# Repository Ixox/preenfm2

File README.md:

# preenfm2 firmware

Ixox/preenfm2 is the official repository of the preenfm2 firmware.

You can find here the compiled firmware, its code source and some hardware files for the PCB, MCU board and cases.

To flash the preenfm2 for the first time, [follow these instructions](https://github.com/Ixox/preenfm2/tree/master/flash)

## Compiling the firmware

To compile the firmware, you'll need [arm-gcc version 4.7](https://launchpad.net/gcc-arm-embedded/+milestone/4.7-2014-q2-update)

Add the bin directory to your PATH, and run **'make'**, you'll get the list of the available targets.

```bash
$ make
You must chose a target 
Don't forget to clean between different build targets
   clean : clean build directory
   pfm : build pfm2 firmware
   pfmcv : build pfm2 firmware for Eurorack 
   installdfu : flash last compiled firmware through DFU
   zip : create zip with all inside
```
Since some refactoring, the bootloader does not compile anymore. But it's available in its binary format.

Then put your preenfm2 in [bootloader mode](http://ixox.fr/preenfm2/manual/upgrade-firmware/). Look at DFU part 4.

To flash the firmware on the preenfm2 using the DFU protocol :

```bash
make installdfu
```

Once it's done, unplug the power cable and plug it back.

## New Filters in 2.11

Many effects have been added in the firmware 2.11. They were coded by [Toltekradiation](http://ixox.fr/forum/index.php?topic=69544.0).

His github repo is [here](https://github.com/pvig/preenfm2). You'll find there some description of the different effects.

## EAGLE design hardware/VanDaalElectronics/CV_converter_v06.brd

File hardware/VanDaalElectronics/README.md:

# Eurorack PCB eagle files for the preenfm2

Here is the first revision Eagle files for the Eurorack daughter board.
This board converts Modulation inputs (cv3 and CV4) -5V to +5V for Preen AIN
It handles V/Oct 0-8V from CV2 to AIN and Gate from CV1 to AIN.

All the unnamed diodes are general purpose diodes.
Shotky diodes are also what ever fits. As long it has very low forward voltage.

CV inputs can be wired straight to 3.5mm jacks.
Same with MIDI and USB.

+5V needs to be routed to the mainboard.

[Van Daal Electronics DIY Kit](https://vandaal-electronics.com/product/preenfm-eurorack-retrofit-diy-kit/)

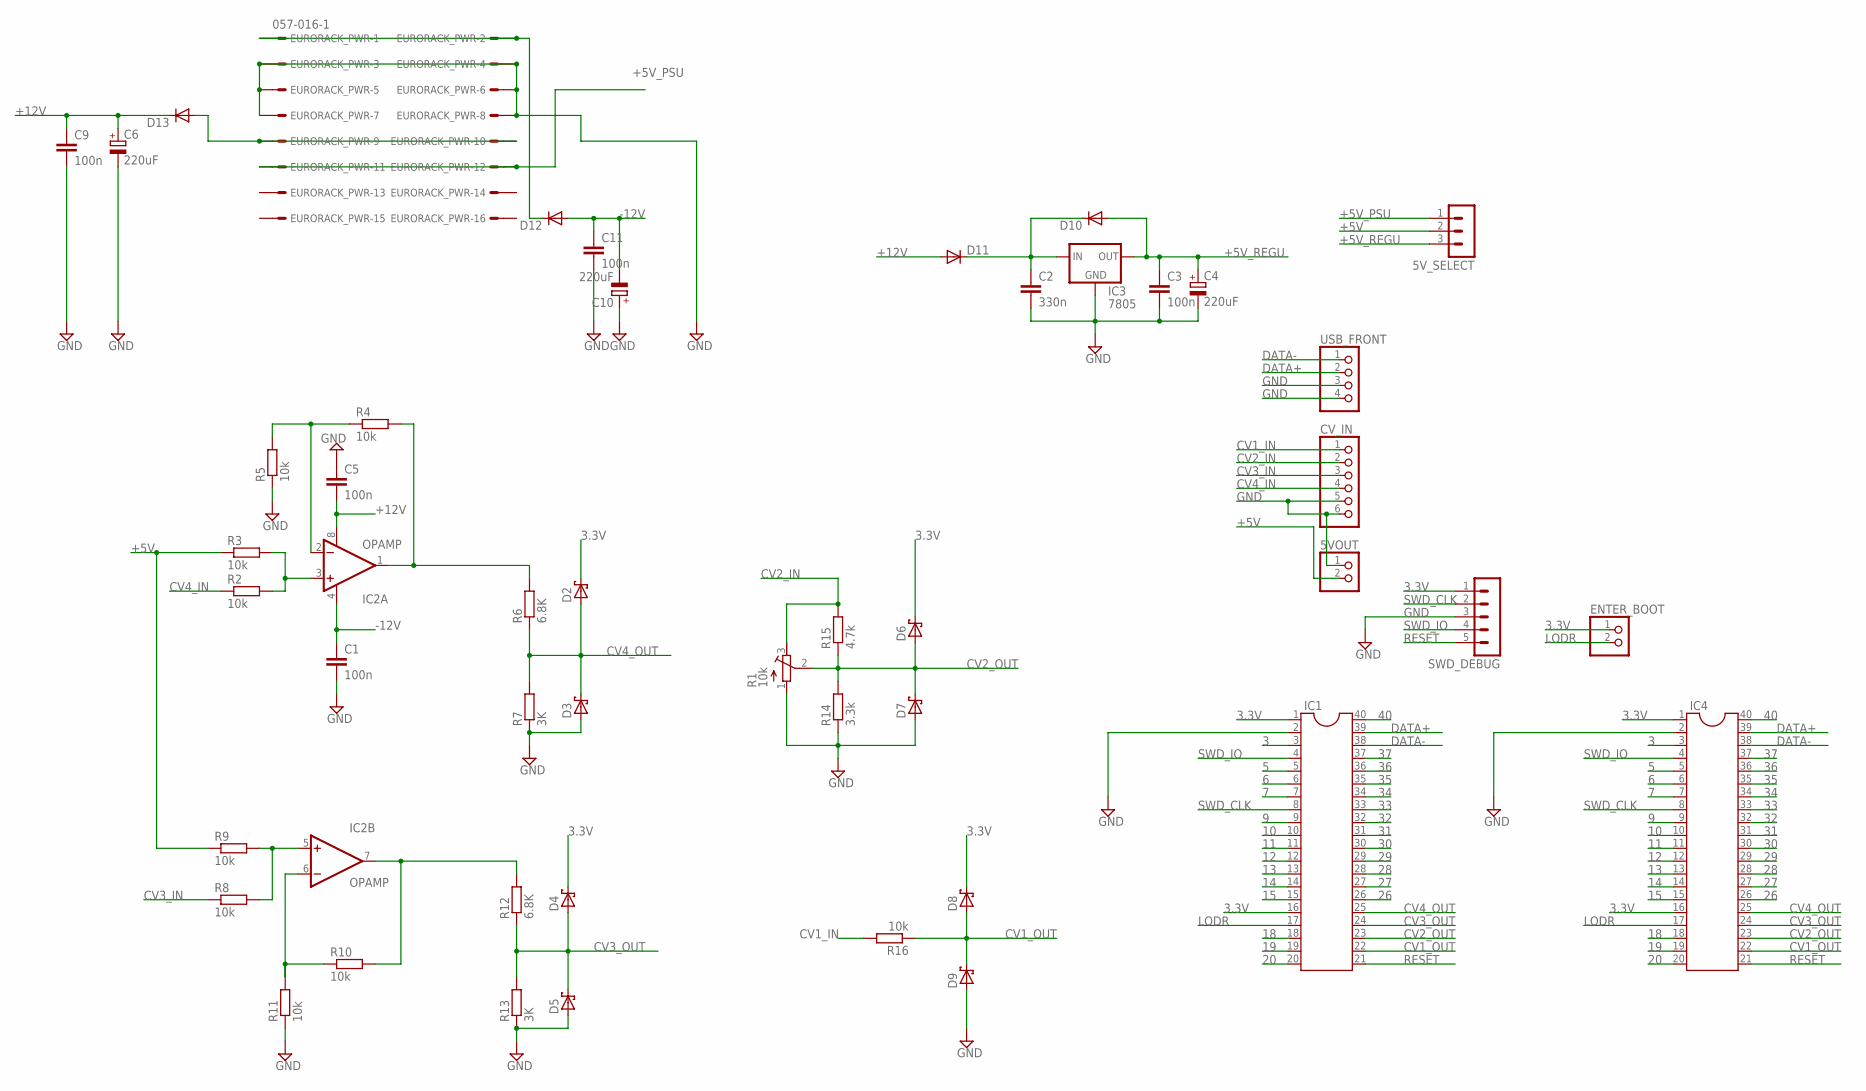
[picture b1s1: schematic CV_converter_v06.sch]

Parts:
5VOUT: PINHD-1X2; 1X02
5V_SELECT: MA03-1
C1, C3, C5, C9, C11: 100n; C025-025X050
C2: 330n; C025-025X050
C4, C6, C10: 220uF; E2,5-7
CV_IN: PINHD-1X6; 1X06
D2, D3, D4, D5, D6, D7, D8, D9: SCHOTTKY-DIODEDO35-7; DO35-7
D10, D11, D12, D13: DIODE-D-7.5; D-7.5
ENTER_BOOT: PINHD-1X2; 1X02
EURORACK_PWR: 057-016-1
IC1, IC4: DIL40
IC2: OPAMP; DIP08
IC3: 7805; TO-220-ALT
R1: 10k; RTRIM64W
R2, R3, R4, R5, R8, R9, R10, R11, R16: 10k; 0207/7
R6, R12: 6.8K; 0207/7
R7, R13: 3K; 0207/7
R14: 3.3k; 0207/7
R15: 4.7k; 0207/7
SWD_DEBUG: MA05-1
USB_FRONT: PINHD-1X4; 1X04

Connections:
3: IC1.3, IC4.3
3.3V: D2.C, D4.C, D6.C, D8.C, ENTER_BOOT.1, IC1.1, IC1.16, IC4.1, IC4.16, SWD_DEBUG.1
5: IC1.5, IC4.5
6: IC1.6, IC4.6
7: IC1.7, IC4.7
9: IC1.9, IC4.9
10: IC1.10, IC4.10
11: IC1.11, IC4.11
12: IC1.12, IC4.12
13: IC1.13, IC4.13
14: IC1.14, IC4.14
15: IC1.15, IC4.15
18: IC1.18, IC4.18
19: IC1.19, IC4.19
20: IC1.20, IC4.20
26: IC1.26, IC4.26
27: IC1.27, IC4.27
28: IC1.28, IC4.28
29: IC1.29, IC4.29
30: IC1.30, IC4.30
31: IC1.31, IC4.31
32: IC1.32, IC4.32
33: IC1.33, IC4.33
34: IC1.34, IC4.34
35: IC1.35, IC4.35
36: IC1.36, IC4.36
37: IC1.37, IC4.37
40: IC1.40, IC4.40
+5V: 5VOUT.2, 5V_SELECT.2, R3.1, R9.1
+5V_PSU: 5V_SELECT.1, EURORACK_PWR.11, EURORACK_PWR.12
+5V_REGU: 5V_SELECT.3, C3.1, C4.+, D10.A, IC3.OUT
+12V: C5.2, C6.+, C9.1, D11.A, D13.C, IC2.8 (V+)
-12V: C1.1, C10.-, C11.1, D12.A, IC2.4 (V-)
CV1_IN: CV_IN.1, R16.2
CV1_OUT: D8.A, D9.C, IC1.22, IC4.22, R16.1
CV2_IN: CV_IN.2, R1.3 (E), R15.2
CV2_OUT: D6.A, D7.C, IC1.23, IC4.23, R1.2 (S), R14.2, R15.1
CV3_IN: CV_IN.3, R8.1
CV3_OUT: D4.A, D5.C, IC1.24, IC4.24, R12.1, R13.2
CV4_IN: CV_IN.4, R2.1
CV4_OUT: D2.A, D3.C, IC1.25, IC4.25, R6.1, R7.2
DATA+: IC1.39, IC4.39, USB_FRONT.2
DATA-: IC1.38, IC4.38, USB_FRONT.1
GND: 5VOUT.1, C1.2, C2.2, C3.2, C4.-, C5.1, C6.-, C9.2, C10.+, C11.2, CV_IN.5, CV_IN.6, D3.A, D5.A, D7.A, D9.A, EURORACK_PWR.3, EURORACK_PWR.4, EURORACK_PWR.5, EURORACK_PWR.6, EURORACK_PWR.7, EURORACK_PWR.8, IC1.2, IC3.GND, IC4.2, R1.1 (A), R5.1, R7.1, R11.1, R13.1, R14.1, SWD_DEBUG.3, USB_FRONT.3, USB_FRONT.4
LODR: ENTER_BOOT.2, IC1.17, IC4.17
unnamed: IC2.1 (OUT), R4.2, R6.2
unnamed: IC2.3 (+IN), R2.2, R3.2
unnamed: C2.1, D10.C, D11.C, IC3.IN
unnamed: IC2.2 (-IN), R4.1, R5.2
unnamed: IC2.6 (-IN), R10.1, R11.2
unnamed: IC2.7 (OUT), R10.2, R12.2
unnamed: IC2.5 (+IN), R8.2, R9.2
unnamed: D12.C, EURORACK_PWR.1, EURORACK_PWR.2
unnamed: D13.A, EURORACK_PWR.9, EURORACK_PWR.10
RESET: IC1.21, IC4.21, SWD_DEBUG.5
SWD_CLK: IC1.8, IC4.8, SWD_DEBUG.2
SWD_IO: IC1.4, IC4.4, SWD_DEBUG.4

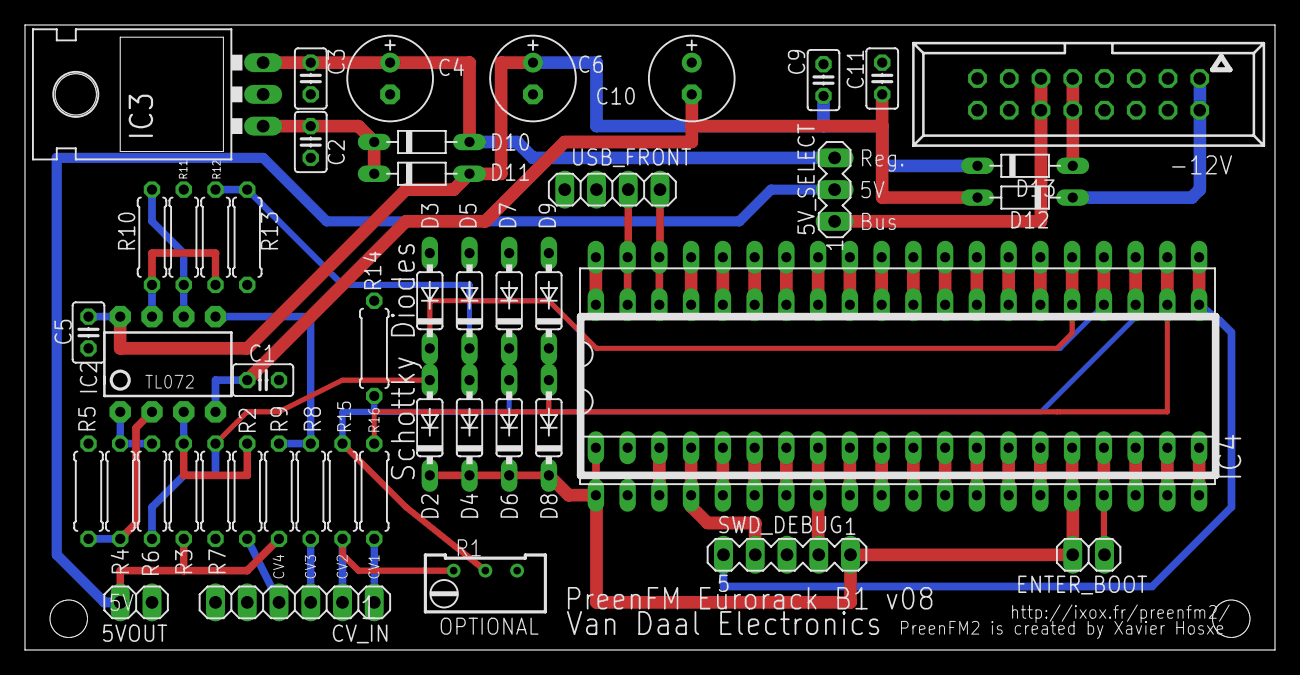
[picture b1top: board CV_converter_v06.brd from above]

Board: 2 copper layers, 100.0 x 50.0 mm, 48 parts (0 on the bottom side), 57 nets.

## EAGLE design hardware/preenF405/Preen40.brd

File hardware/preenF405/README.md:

'''html
### PreenF405

Here is the schematic and board of the preenFM microcontroller board.
Files have been created with eagle 6.5.

The BOM used for the official preenF405 is :
<pre>
Manufacturer       Part Number         Designator        Qty  Desciption                       Case            Top/bot Points
Yageo              CC0603KRX7R9BB104   C1, C2, C3, C4    4    100nF,50V,10%,X7R,0603           0603     SMD    Top     2    
Murata             GRM1885C1H200FA01D  C6, C7            2    20pF,50V,1%,C0G,0603             0603     SMD    Top     2    
TDK Corporation    C2012X7R1H225K125AC C8, C9            2    2.2uF,50V,10%,X7R,0805           0805     SMD    Top     2    
Kemet              T491B106K016AT      C10               1    10uF,16V,10%,1411(B)             1411(B)  SMD    Top     2    
Yageo              RC0603FR-0710KL     R1, R2, R3, R6    4    10K,1%,1/10W,0603                0603     SMD    Top     2    
Yageo              RC0603FR-0722RL     R4, R5            2    22R,1%,1/10W,0603                0603     SMD    Top     2    
TXC Corporation    AT-12.000MAGK-T     QA                1    12MHz,20pF,HC49/US               HC49/US  SMD    Top     2    
STMicroelectronics STM32F405RGT6       IC1               1    STM32F405RGT6,64-LQFP            64-LQFP  SMD    Top     64   
TAD                1-2001FBV0T                           2    1*20 Pins,Pitches 2.54mm,180°                    Bot     20   
</pre>

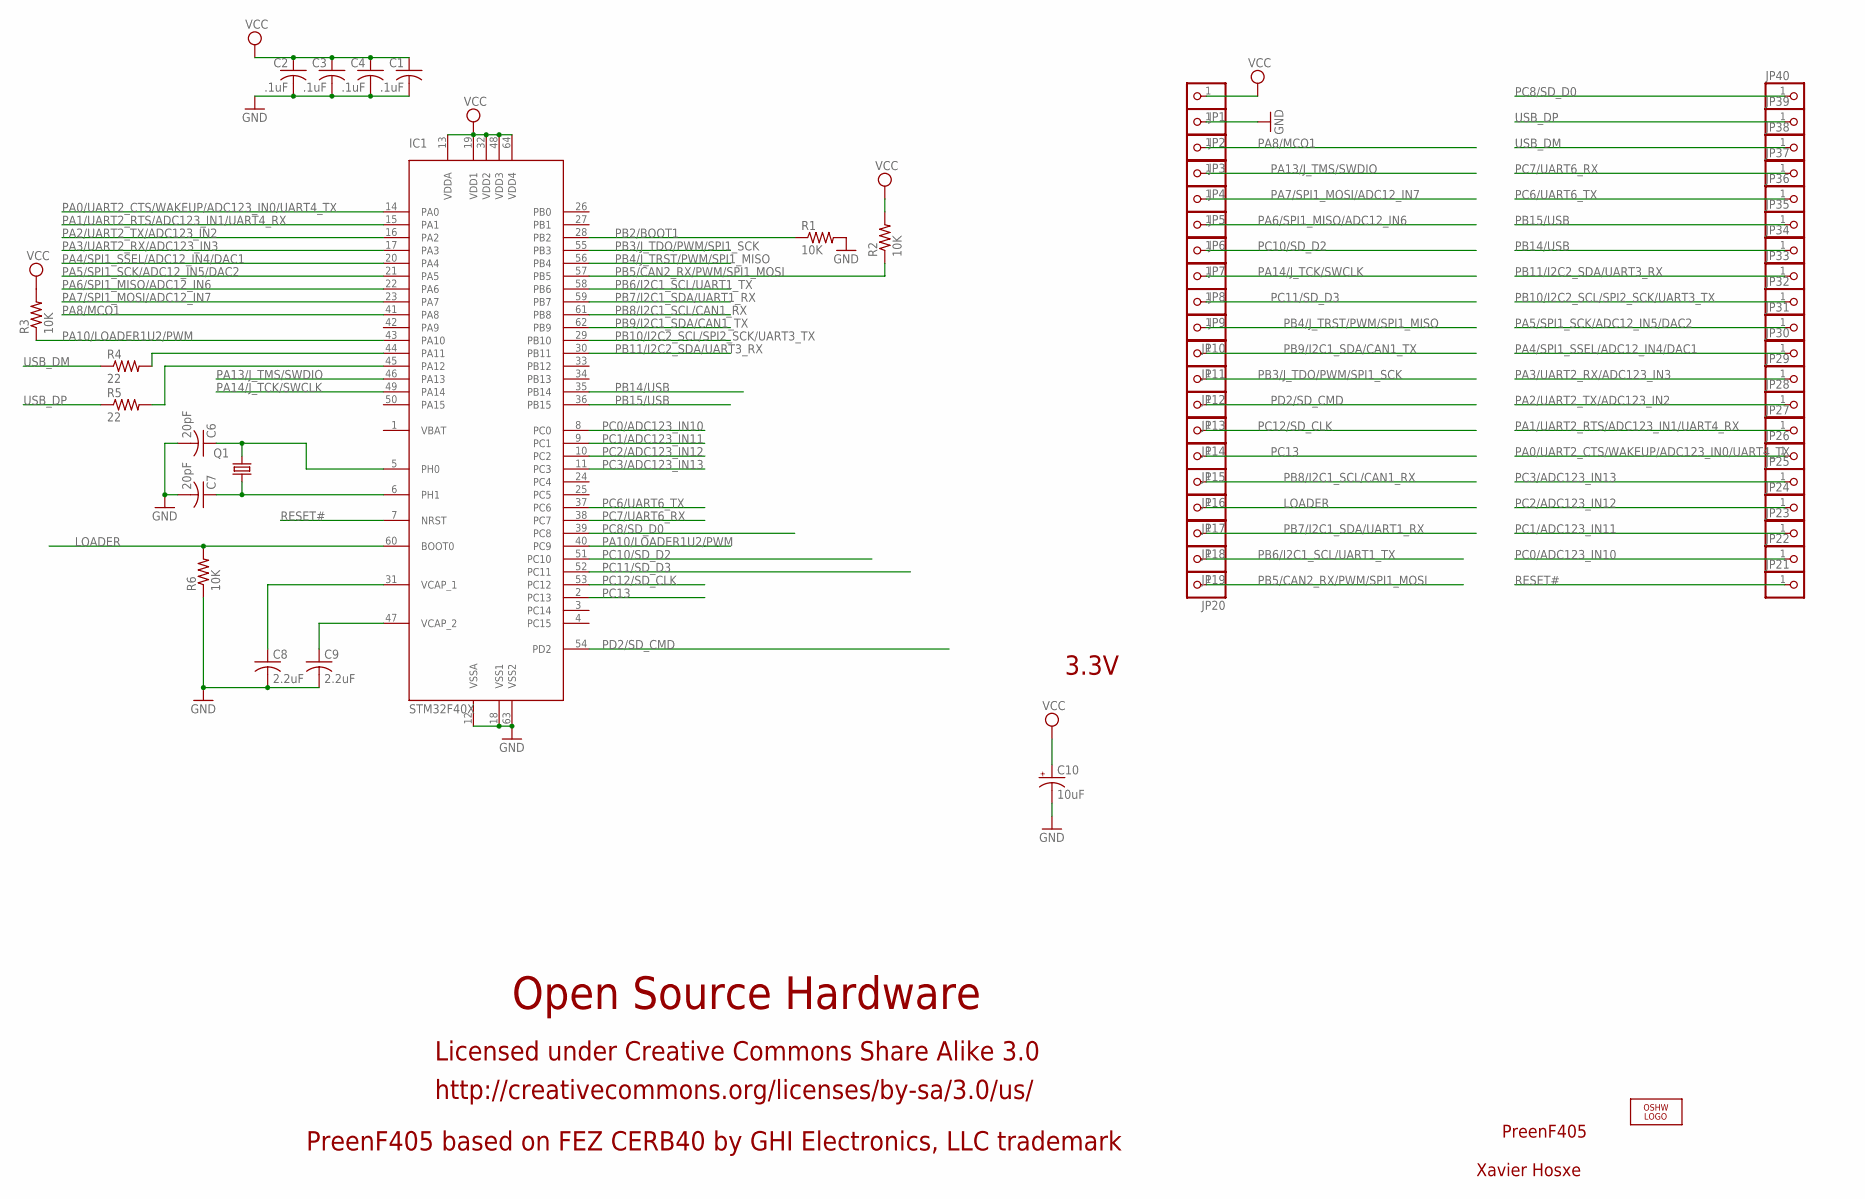
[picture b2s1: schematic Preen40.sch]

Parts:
C1, C2, C3, C4: .1uF; C0603K
C6, C7: 20pF; C0603K
C8, C9: 2.2uF; C0805K
C10: 10uF; CT3528
IC1: STM32F40X; LQFP64
JP1, JP2, JP3, JP4, JP5, JP6, JP7, JP8, JP9, JP10, JP11, JP12, JP13, JP14, JP15, JP16, JP17, JP18, JP19, JP20, JP21, JP22, JP23, JP24, JP25, JP26, JP27, JP28, JP29, JP30, JP31, JP32, JP33, JP34, JP35, JP36, JP37, JP38, JP39, JP40: PINHD-1X1; 1X01
LOGO1: LOGO-OSHW-FILLX0200-NT; OSHW_FILLX200_NOTEXT
Q1: 12Mhz; SM49@1
R1, R2, R3, R6: 10K; R0603
R4, R5: 22; R0603

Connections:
GND: C1.2, C2.2, C3.2, C4.2, C6.2, C7.2, C8.2, C9.2, C10.-, IC1.12 (VSSA), IC1.18 (VSS1), IC1.63 (VSS2), JP2.1, R1.2, R6.1
LOADER: IC1.60 (BOOT0), JP17.1, R6.2
unnamed: C9.1, IC1.47 (VCAP_2)
unnamed: C8.1, IC1.31 (VCAP_1)
unnamed: IC1.44 (PA11), R4.2
unnamed: IC1.45 (PA12), R5.2
PA0/UART2_CTS/WAKEUP/ADC123_IN0/UART4_TX: IC1.14 (PA0), JP26.1
PA1/UART2_RTS/ADC123_IN1/UART4_RX: IC1.15 (PA1), JP27.1
PA2/UART2_TX/ADC123_IN2: IC1.16 (PA2), JP28.1
PA3/UART2_RX/ADC123_IN3: IC1.17 (PA3), JP29.1
PA4/SPI1_SSEL/ADC12_IN4/DAC1: IC1.20 (PA4), JP30.1
PA5/SPI1_SCK/ADC12_IN5/DAC2: IC1.21 (PA5), JP31.1
PA6/SPI1_MISO/ADC12_IN6: IC1.22 (PA6), JP6.1
PA7/SPI1_MOSI/ADC12_IN7: IC1.23 (PA7), JP5.1
PA8/MCO1: IC1.41 (PA8), JP3.1
PA10/LOADER1U2/PWM: IC1.40 (PC9), IC1.43 (PA10), R3.1
PA13/J_TMS/SWDIO: IC1.46 (PA13), JP4.1
PA14/J_TCK/SWCLK: IC1.49 (PA14), JP8.1
PB2/BOOT1: IC1.28 (PB2), R1.1
PB3/J_TDO/PWM/SPI1_SCK: IC1.55 (PB3), JP12.1
PB4/J_TRST/PWM/SPI1_MISO: IC1.56 (PB4), JP10.1
PB5/CAN2_RX/PWM/SPI1_MOSI: IC1.57 (PB5), JP20.1, R2.1
PB6/I2C1_SCL/UART1_TX: IC1.58 (PB6), JP19.1
PB7/I2C1_SDA/UART1_RX: IC1.59 (PB7), JP18.1
PB8/I2C1_SCL/CAN1_RX: IC1.61 (PB8), JP16.1
PB9/I2C1_SDA/CAN1_TX: IC1.62 (PB9), JP11.1
PB10/I2C2_SCL/SPI2_SCK/UART3_TX: IC1.29 (PB10), JP32.1
PB11/I2C2_SDA/UART3_RX: IC1.30 (PB11), JP33.1
PB14/USB: IC1.35 (PB14), JP34.1
PB15/USB: IC1.36 (PB15), JP35.1
PC0/ADC123_IN10: IC1.8 (PC0), JP22.1
PC1/ADC123_IN11: IC1.9 (PC1), JP23.1
PC2/ADC123_IN12: IC1.10 (PC2), JP24.1
PC3/ADC123_IN13: IC1.11 (PC3), JP25.1
PC6/UART6_TX: IC1.37 (PC6), JP36.1
PC7/UART6_RX: IC1.38 (PC7), JP37.1
PC8/SD_D0: IC1.39 (PC8), JP40.1
PC10/SD_D2: IC1.51 (PC10), JP7.1
PC11/SD_D3: IC1.52 (PC11), JP9.1
PC12/SD_CLK: IC1.53 (PC12), JP14.1
PC13: IC1.2 (PC13), JP15.1
PD2/SD_CMD: IC1.54 (PD2), JP13.1
RESET#: IC1.7 (NRST), JP21.1
USB_DM: JP38.1, R4.1
USB_DP: JP39.1, R5.1
VCC: C1.1, C2.1, C3.1, C4.1, C10.+, IC1.13 (VDDA), IC1.19 (VDD1), IC1.32 (VDD2), IC1.48 (VDD3), IC1.64 (VDD4), JP1.1, R2.2, R3.2
XTAL3: C6.1, IC1.5 (PH0), Q1.2
XTAL4: C7.1, IC1.6 (PH1), Q1.1

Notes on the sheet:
PreenF405
Xavier Hosxe
Open Source Hardware
Licensed under Creative Commons Share Alike 3.0
PreenF405 based on FEZ CERB40 by GHI Electronics, LLC trademark
http://creativecommons.org/licenses/by-sa/3.0/us/
3.3V

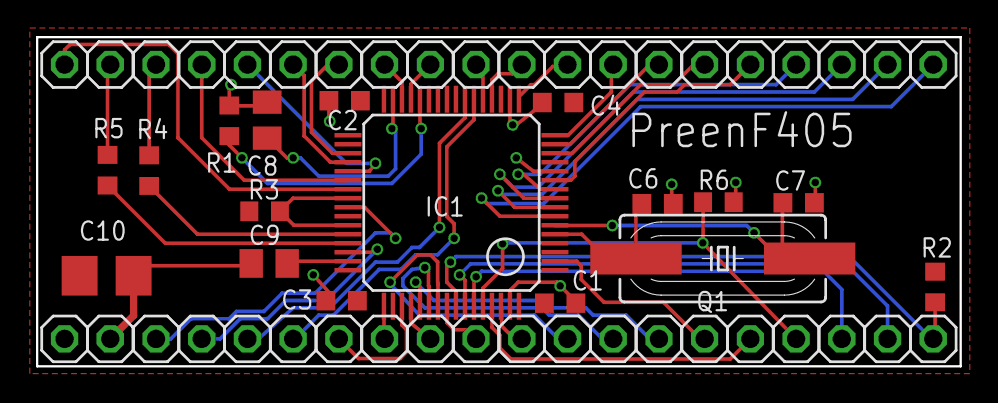
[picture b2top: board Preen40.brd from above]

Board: 2 copper layers, 51.3 x 18.3 mm, 58 parts (1 on the bottom side), 48 nets.

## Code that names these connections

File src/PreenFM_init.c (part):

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    // GPIOG Periph clock enable
    RCC_AHB1PeriphClockCmd(RCC_AHB1Periph_GPIOB, ENABLE);

    /* Configure PB5 in output mode */
    GPIO_InitTypeDef GPIO_InitStructure;
    GPIO_InitStructure.GPIO_Pin = LEDPIN;
    GPIO_InitStructure.GPIO_Mode = GPIO_Mode_OUT;
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    /* Enable DMA2, thats where ADC is hooked on -> see Tab 20 (RM00090) */
    RCC_AHB1PeriphClockCmd(RCC_AHB1Periph_GPIOC | RCC_AHB1Periph_DMA2, ENABLE);

    /* Initialise GPIOs C0 (ADC123_IN10), C1 (ADC123_IN11), C2 (ADC123_IN12)*/
    GPIO_StructInit(&GPIO_InitStructure);
    GPIO_InitStructure.GPIO_Pin   = GPIO_Pin_0 | GPIO_Pin_1 | GPIO_Pin_2 | GPIO_Pin_3;
    GPIO_InitStructure.GPIO_Mode  = GPIO_Mode_AIN;
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    RCC_AHB1PeriphClockCmd(RCC_AHB1Periph_GPIOA | RCC_AHB1Periph_GPIOB | RCC_AHB1Periph_GPIOC, ENABLE);

    /**I2S3 GPIO Configuration    
    PC7     ------> I2S3_MCK
    PA15     ------> I2S3_WS
    PC12     ------> I2S3_SD
    PB3     ------> I2S3_CK 
    */

    /* Connect SPI pins to AF5 */
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
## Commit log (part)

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2014-01-16 Fixed velocity in ALGO17 & 18
2014-01-18 First FX commit : LP, HP, Bass, Mono.
2014-01-18 FX default value cannot be (0,0,0,0)
2014-01-26 1.B2 : fix + new mixer + CC as source + OLED screen saver + New LFO
2014-02-01 Better navigation with double press in Matrix menu
2014-02-04 1.B4 Better DX7 import
2014-02-06 New hardfault page
2014-02-06 Fixed voice allocation bugs. getFreeVoice + Timbre::preenNewNote.
2014-03-05 1.B6 : fixed glide display bug + USB aftertouch Iternal refactoring
2014-03-11 Add direction 'played' to arpeggiator
2014-03-12 1.B7 : Fixed channe 3&4 but
2014-03-13 1.B8 : arpeggiator as played + note on alocation reworked
2014-03-15 Silence warnings...
2014-03-15 Less verbose makefile
2014-03-16 Bootloader 1.11
2014-03-16 Better push timer for bootloader
2014-03-20 1.B9... Makefile & TODO updated
2014-03-20 ALGO28 : only show IM1
2014-03-22 1.B9: Bank, BankLSB and program change implemented.
2014-03-23 Removed ugly Display debug
2014-03-23 Correct version : 1.B10
2014-03-26 1.B11 : LFO.Ksyn => 16.0s + several small fixes in the LF area
2014-03-28 Experimental user-defined pattern for arpeggiator
2014-03-28 Rename engineApr to engineArp (probably just a typo)
2014-03-28 Store user arp pattern (contents might still change though)
2014-03-29 Store arpeggiator patterns in a uint32_t instead of 4 floats, allowing for 4 per timbre. Add specific editing code (rough implementation)
2014-04-02 Performance patch: mostly from Patrick perf Dowling branch.
2014-04-03 Makefile 1.B12 + KSyn display fixe bug (4.00 correctly displayed)
2014-04-09 Ensure valid menu row when switching instruments, return to last state
2014-04-10 Fix boundary case of navigation, move #define to header
2014-04-10 Change compile-time edit option a run-time configurable setting; rename to 'unlinked' editing so false default works
2014-04-11 Fix typo in matrix target (Mix3/pan3)
2014-04-12 Fix regression in navigation and use correct button for env rows
2014-04-12 Add comment
2014-04-27 Add cyclic modes for arpeggiator
2014-04-29 Minor cleanup, rename arp modes
2014-05-02 Remove unused virtual function calls, save some cycles...
2014-05-02 Remove useless code + move code to cpp
2014-05-03 Patrick bug fix
2014-05-07 Midi CC fix
2014-05-16 Firmware 1.00 ready ?
2014-06-05 Fix combo problem + firmware 1.01
2014-06-17 StepSequers & preset name flushed with presets
2014-06-29 Better name refresh
2014-07-15 Swap to page shortcuts
2014-07-15 1.03 : nrpn preset flush are now done correctly on the right midi channel
2014-08-10 Small insignifiant details
2014-09-08 Randomizer + boot sound
2014-09-08 BP middle freq is targetable from the Matrix
2014-10-12 Fix LFO with ksyn = 0.01
2015-08-09 1.07b1 Scala
2015-08-11 compilation error on Linux fixed.
2015-08-11 Lfo phases + Midi note scaling
2015-08-17 Real polyphony
2015-08-18 Fix Modwheel, Pitchbend bug
2015-08-19 1.99c : 2 midi note scales + Gate back
2015-08-20 1.99c : matrix target list updated
2015-08-27 1.99d save
2015-08-28 2.00b1 see TODO.txt
2015-08-28 2.00b1 last minute change :(
2015-10-05 First version of user waveforms
2015-10-10 All waveforms between -1.0 and 1.0
2015-10-15 2.02 : user waveform preprocessing
2016-05-08 2.03 : more CC
2016-08-24 2.05B3
2016-09-14 Breath CC to matrix source
2016-09-14 FIX : IM* target matrix can correctly decrease velocity IM
2016-09-19 Strict NRPN option added : use 7bits (CC6 only) when sufficient
2016-09-24 PreenF405 README
2016-10-11 Revert "Strict NRPN option added : use 7bits (CC6 only) when sufficient"
    This reverts commit 4ffa40c3e819c186cf1b49844e744488c2d04e78.
2016-10-12 New midi CC for arpegiator
2016-10-12 Fix missing note... Stupid return instead of continue :/
2016-10-12 2.06
2016-11-16 New svg case files
2016-11-17 hardwae/case : hardware list added
2016-11-17 Create gh-pages branch via GitHub
2016-12-16 Fix MTX* problem
2017-05-29 PCB r5d files added
2017-05-29 Better README.md
2017-07-12 Add preenF405 detailed BOM
2017-10-15 Copy feature
2017-10-16 Lokki's feature : global midi channel + hertz osc detune
2017-10-22 2.08b2 lfo rate up to 99.9hz +fixes
2017-10-23 2.08b3 : add CC for env modulators and carriers
2017-10-23 release/fw_2.08b3 firmware
2017-10-24 Matrix destination can control Carrier vs Modulatir Env*
2017-10-24 Firmware 2.08b4
2017-11-05 Fix NRPN step sequencer
2017-11-05 2.08 binary added
2017-11-05 2.08 REAMDE.md
2017-11-05 2.08 README.md changes
2017-11-07 CC cannot make filter Freq and Res > 1.00
2018-04-02 2.08b env bug fix
2018-10-13 Scala Enabled and Scale controlable through midi CC
2018-10-13 Fix Op 1&4 default combo release time
2018-10-13 2.08c was already used
2018-10-14 Reset internal cached values between notes
2018-10-27 Prevent reading null pointer when receiving midi value > max
2018-10-27 Move ARP CC to 100+ to prevent confustion with NRPN
2018-10-27 Update correctly * (preset modified) for instruments not on screen
2018-10-27 Display refresh optimisation on midi update + fix some preset display that show up when it should not
2018-12-31 Update to latest 4.7 gcc release.
2019-03-08 Van Daal Electronics CB converter PCB added
2019-03-08 Update URL
2019-04-03 Welcome Emilie in the preenfm2 code
2019-05-04 Schematics in pdf
2019-05-30 New combo bank now shows up correctly
2019-05-30 New midi channel for current instrument + new CC(119) to modify current instrument
2019-05-30 New case svg files added
2019-05-30 Analog in of P3 enabled
2019-05-30 Fix bug with Gate On when switch on
2019-05-30 Eurorack + gate + v/oct + tunable
2019-05-30 Fix Makefile
2019-05-30 Put back modifiable CV gate
2019-05-30 CVGate can trigger several instruments
2019-08-08 new filter flavour + tilt filter
2019-08-08 added lost commit
2019-08-09 tilt fix
2019-08-10 some filter tweak+code cleaning
2019-08-10 added allpass, saturator & sigmoid filters
2019-08-11 sigmoid tweak
2019-08-11 more usable range for saturator
2019-08-11 allpass filter used for a stereo enhancer filter
2019-08-13 dist & sigmoid tweak
2019-08-14 added xor & foldback distortion
2019-08-15 fixed sigmoid level + changed fold algo
2019-08-15 missing matrix filter controls added
2019-08-15 lowered resonance in tilt filter
2019-08-16 lp2 & hp2 reso saturation fix
2019-08-17 various optimizations & waveshaping here and here
2019-08-17 wrap filter added
2019-08-18 added swap~ fx + threshol voicenum attenuation
2019-08-18 fx threshold tweak
2019-08-21 hp2 bug fix + texture fx try + some tweak
2019-08-22 changed fx swap and texture to texture1 & 2 = bitmangling fx
2019-08-22 allow texture1&2 to be matrix controlled
2019-08-25 added lphp filter
2019-08-26 added BP3 + sorted fx list by use (more or less)
2019-08-26 edited readme + LPws
2019-08-26 readme update
2019-08-27 added notch & lp3 filters
2019-08-28 added PEAK, HP3, BP3 + renamed old BP3 -> BPds
2019-08-29 added bell filter
2019-08-29 various tweak + readme update
2019-08-30 wrap & fold rework + code cleaning
2019-08-30 added tone to distortion fx + tweak
2019-08-30 optimisation
2019-08-31 lp2&hp2 offset
2019-08-31 svf volume compensation
2019-09-01 code cleaning
2019-09-01 lphp & BPds resonance tweak
2019-09-02 added lowshelf & highshelf filters
2019-09-04 drastic optimizations
2019-09-05 float cast optimization
2019-09-06 sat33, sigmoid, lp resonance tweak
2019-09-10 sig, fold, wrap filter change
2019-09-11 sigm, fold, wrap
2019-09-13 FILTER_LPXOR rework
2019-09-21 svf filters cleanup, added LPSin, HPSin, BPSin
2019-09-25 lpsin now use svf lp
2019-09-27 satSin fix + optimization
2019-09-29 added doublenotch + optimization
2019-10-04 reworked pann, ap3
2019-10-05 resonant 3xap, tilt ap, sat ap, 3xnoth ap3 pan
2019-10-05 texture1&2 : added ap diffusion
2019-10-06 textures slight mod + rollback some ap filters
2019-10-10 AP4D : Diffusion allpass filter + ap fx tweak
2019-10-12 ap on svf + various tweak
2019-10-18 allpass allpass
2019-10-23 formantic filter + ap polish
2019-10-26 formant filter wip
2019-10-27 formant + ap4 fine tune
2019-11-01 tanh optimization, formant filter tweak
2019-11-05 added ladder filter
2019-11-19 wip oryx2, ladders..
2019-11-21 oryx + ladders wip
2019-11-24 formant wip
2019-11-25 formants fine tune
2019-11-30 added h3o+ filter
2019-12-01 h3o+ wip
2019-12-05 various tweak
2019-12-07 srr + tb wip
2019-12-08 tb2 + crush2 wip
2019-12-09 code cleaning + tbcrunchtweak
2019-12-10 crush wip
2019-12-11 reworked srrx2 & Svh3
2019-12-12 Alkx fine tuning
2019-12-14 Put back original README + filters part added
2019-12-14 Fix possible problem when number of voice is increased
2019-12-14 fix to allow adcIn merge
2019-12-14 velocity fix + code cleaning
2019-12-14 h3o+ : remove accent circuit
2019-12-14 accent is back on teebee filter
2019-12-15 bpds self oscillation fix
2019-12-15 18db resonance tweak
2019-12-15 peak reso curve tweak
2020-01-09 added 8 matrix sources
2020-01-09 matrixSourcePosition for CVIN fix
2020-01-11 README : makefile target list updated
2020-01-11 Add bootloader bin in zip file
2020-01-14 renamed source + oryx rollbck
2020-01-17 why not [more matrix sources] ?
2020-01-20 oryx3 rework + sources
2020-01-26 texture2 rework &+
2020-02-04 textures wip + sin f control
2020-02-05 fine tune levels
2020-02-08 filter controls wip
2020-02-09 lp3, rot
2020-02-19 + glide gate
2020-02-21 rot fix
2020-02-28 glide wip
2020-03-08 better glide
2020-03-16 articulation121
2020-03-20 glide skew...
2020-03-25 hold pb fix
2020-03-26 code cleanup
2020-03-27 end existing gliding in all cases
2020-03-28 stop voice assignation bouncing
2020-03-29 +2 more glide vals
2020-04-04 glide mods fix &+
2020-04-05 2.11 : new instrunet selection for Eurorack version
2020-04-06 mono glide over poly + cleaning
2020-04-06 polyglide branch
2020-04-15 added editor xml definitions
2020-04-30 modulator env loop
2020-05-01 added sustain in env loop
2020-05-07 bug fix & optimisation
2020-05-08 matrix seq start bug fix
2020-05-21 Destination 2 added
2020-05-21 Features from Patrice Vigouroux
2020-05-22 Dedicated #define for CPU_USAGE
2020-05-22 Fix typ
2020-05-22 Fix Dest2 lfoused for MX1/MX4
2020-05-22 Beta1 ready
2020-05-24 updates from 2.12
2020-05-27 more consistent step start result
2020-05-27 updated version
2020-05-29 stepseq fix for ENV_ATTACK destinations
2020-06-28 Not working yet
2020-06-28 Compiles
2020-07-03 CC10 & CC7 & 3 bug fixes
2020-07-03 Remove BOOTLOADER define
2020-07-04 IRQ/DMA ready to test
2020-07-04 2.12 bug fix
2020-07-05 removed GLIDE_ for lighter cpu charge
2020-07-07 Next step
2020-07-09 CS4344 fix IRQ and Frequencies
2020-07-11 matrix dest label fix
2020-07-12 Bootloader read UsbKey and DFU OK
2020-07-14 USB optimization
2020-07-22 Optimization GPIO / LCD / USART
2020-08-15 CS4344 fixes
2020-08-16 Samples are uint32 / CS4344 real 24 bits / Wait with message if no USB Key
2020-08-18 Flash README
2020-08-21 Message when no Usb Key instead of freezing
2020-08-21 CC10 & CC7 / 3 bug fixed / 192Mhz is the new default
2020-08-21 Mix4/Pan4 destination fixed / small optimization
2020-08-21 CS4344
2020-09-19 Better midi and screen boot
2020-09-20 bootlader 1.12 OK
2020-10-03 stutil debug json files
2020-10-16 Upgrade to FatFs 0.14
2020-10-25 Leave more time to USB stick to init before displaying message
2020-10-25 Fix first bit problem with i2s (sound saturation)
2020-10-25 Bootloader 1.13 (not finished)
2020-10-25 Fix screensaver
2020-10-27 Bootloader modificaiton (USB access still does not work)
2020-10-28 Bootloader 1.13 with USB access working
2020-11-06 flash/README updated
2020-11-06 flash README.md updated
2020-11-06 3D printed case added
2020-11-06 update case3DPrint/README
2021-02-15 Unisons seems to work
2021-02-16 Bug fix : load preset freeze + button shortcut
2021-02-16 Fix bug : UI + presets
2021-02-21 Unisons : CV fixed + different starting phase per voice
2021-02-22 Correct initialization of unison phases
2021-02-22 Better unison phases + stop unison when changing number of voices
2021-03-06 Add midi CC (13,14) for unison spread and detune
2021-03-20 2.21 + stop sound when changing play mode (poly/unison)
2021-03-28 Top Surface PCB v1.0
2021-04-13 Fix non-pfm2 sysex problem
2021-04-13 Update debug name
2021-04-17 Case_PCB readme added
2021-04-17 CASE_PCB added picture
2021-08-22 2.21b : Fix Attk midi CC
2024-01-19 vosim like
2024-01-20 algo display + mod range
2024-01-20 lfo noise shape

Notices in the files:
src/PreenFM_init.c:
Copyright 2013
This program is free software: you can redistribute it and/or modify
it under the terms of the GNU General Public License as published by
the Free Software Foundation, either version 3 of the License, or
(at your option) any later version.
parts and their libraries:
SparkFun-AnalogIC: Licensing: CC v3.0 Share-Alike You are welcome to use this library for commercial purposes.
